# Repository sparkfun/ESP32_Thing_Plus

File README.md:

SparkFun ESP32 Thing Plus
========================================

[*SparkFun ESP32 Thing Plus (WRL-15663)*](https://www.sparkfun.com/products/15663)

The [SparkFun ESP32 Thing Plus](https://www.sparkfun.com/products/15663) is a comprehensive development platform for [Espressif's ESP32](https://espressif.com/en/products/hardware/esp32/overview). Like the 8266 and ESP32 Thing, the ESP32 Thing Plus is a **WiFi**-compatible microcontroller with support for **Bluetooth low-energy** (i.e BLE, BT4.0, Bluetooth Smart), a Qwiic adapter, and 21 I/O pins. Add to that a rich set of peripherals ranging from capacitive touch sensors, SD card interface, Ethernet, high-speed SPI, UART, I2S and I<sup>2</sup>C.

Upgraded and easy to use, the Esp32 Thing Plus will help make it the foundation of IoT and connected projects for many years to come.

Repository Contents
-------------------

* **/Hardware** - Eagle design files (.brd, .sch)
* **/Production** - Production panel files (.brd)

Documentation
--------------
* **[Hookup Guide](https://learn.sparkfun.com/tutorials/esp32-thing-plus-hookup-guide)** - Basic hookup guide for the ESP32 Thing Plus.
* **[SparkFun Fritzing repo](https://github.com/sparkfun/Fritzing_Parts)** - Fritzing diagrams for SparkFun products.
* **[SparkFun Graphical Datasheets](https://github.com/sparkfun/Graphical_Datasheets)** -Graphical Datasheets for various SparkFun products.

Product Versions
----------------
* [WRL-15663](https://www.sparkfun.com/products/15663)- v2.0, Slight hardware update that includes a 10&ohm; series resistor between VUSB and CP2102
* [WRL-14689](https://www.sparkfun.com/products/14689)- v1.0, Initial Release

License Information
-------------------

This product is _**open source**_! 

Please review the LICENSE.md file for license information. 

If you have any questions or concerns on licensing, please contact technical support on our [SparkFun forums](https://forum.sparkfun.com/viewforum.php?f=152).

Distributed as-is; no warranty is given.

- Your friends at SparkFun.

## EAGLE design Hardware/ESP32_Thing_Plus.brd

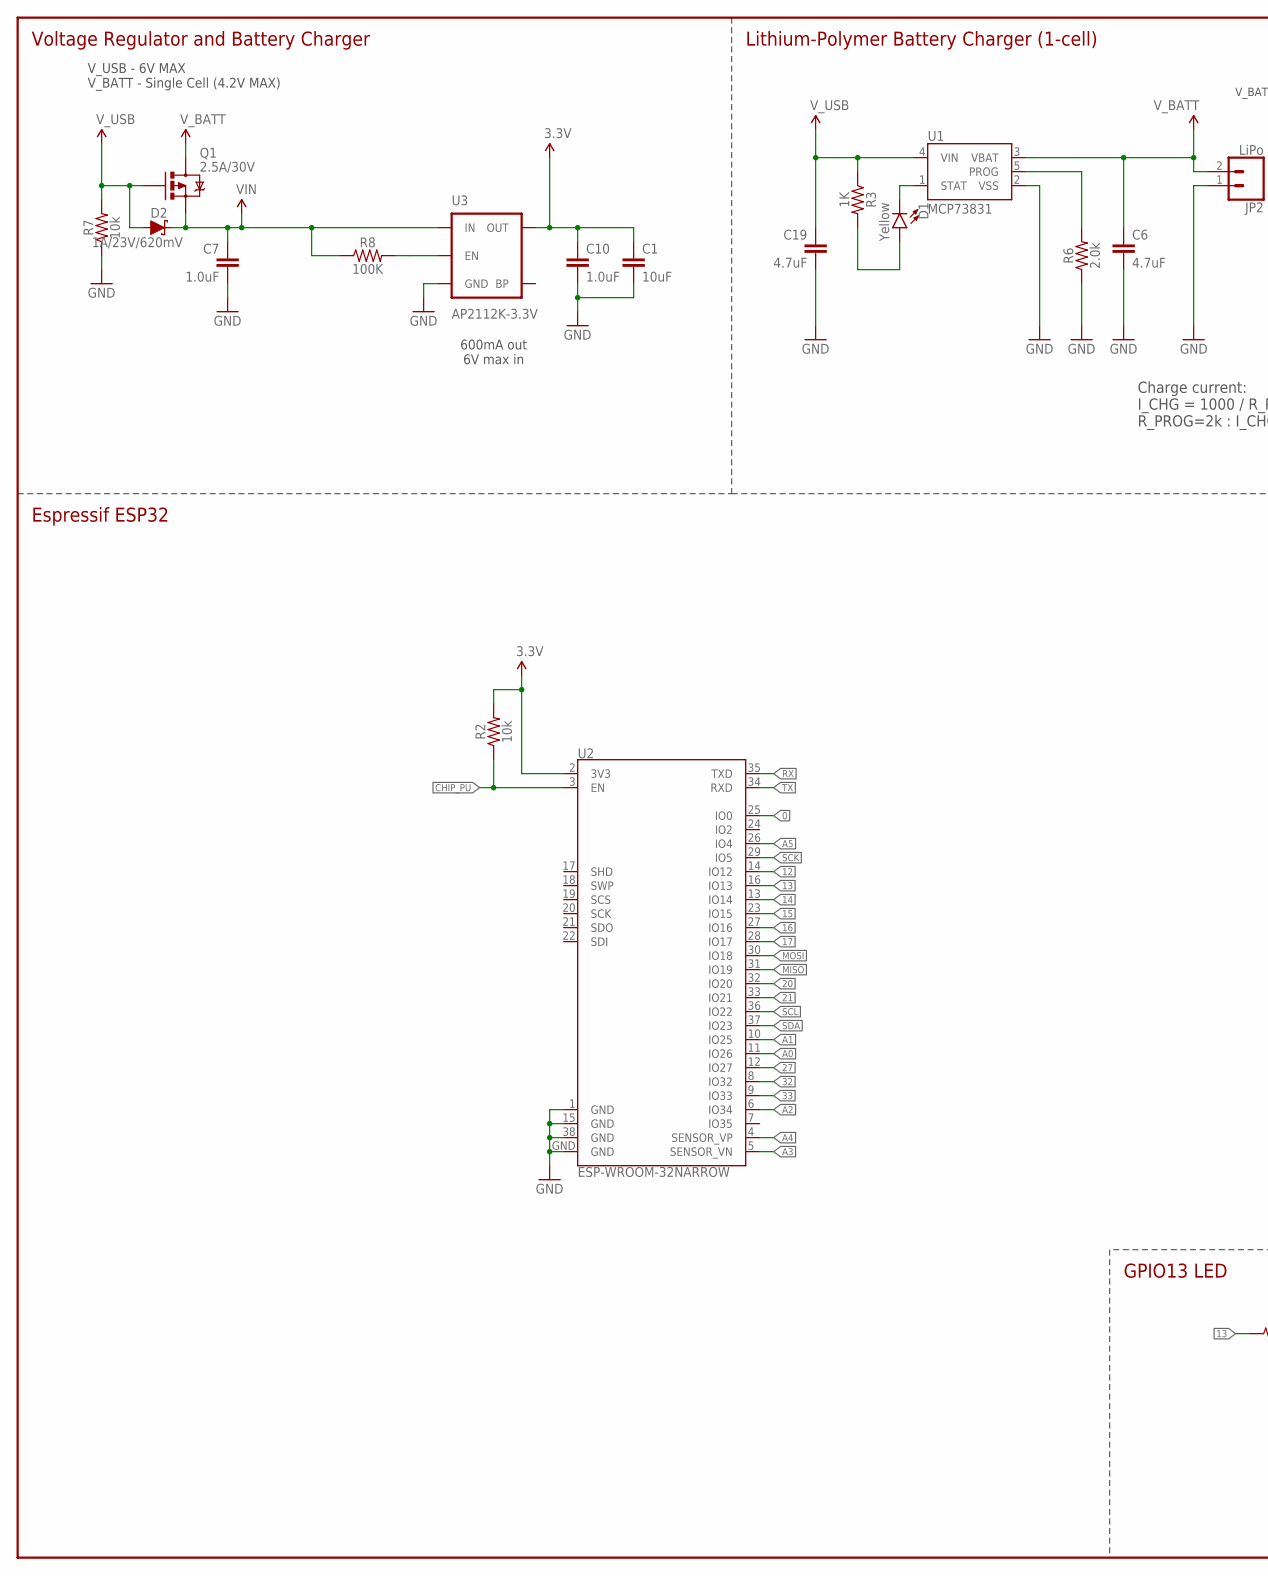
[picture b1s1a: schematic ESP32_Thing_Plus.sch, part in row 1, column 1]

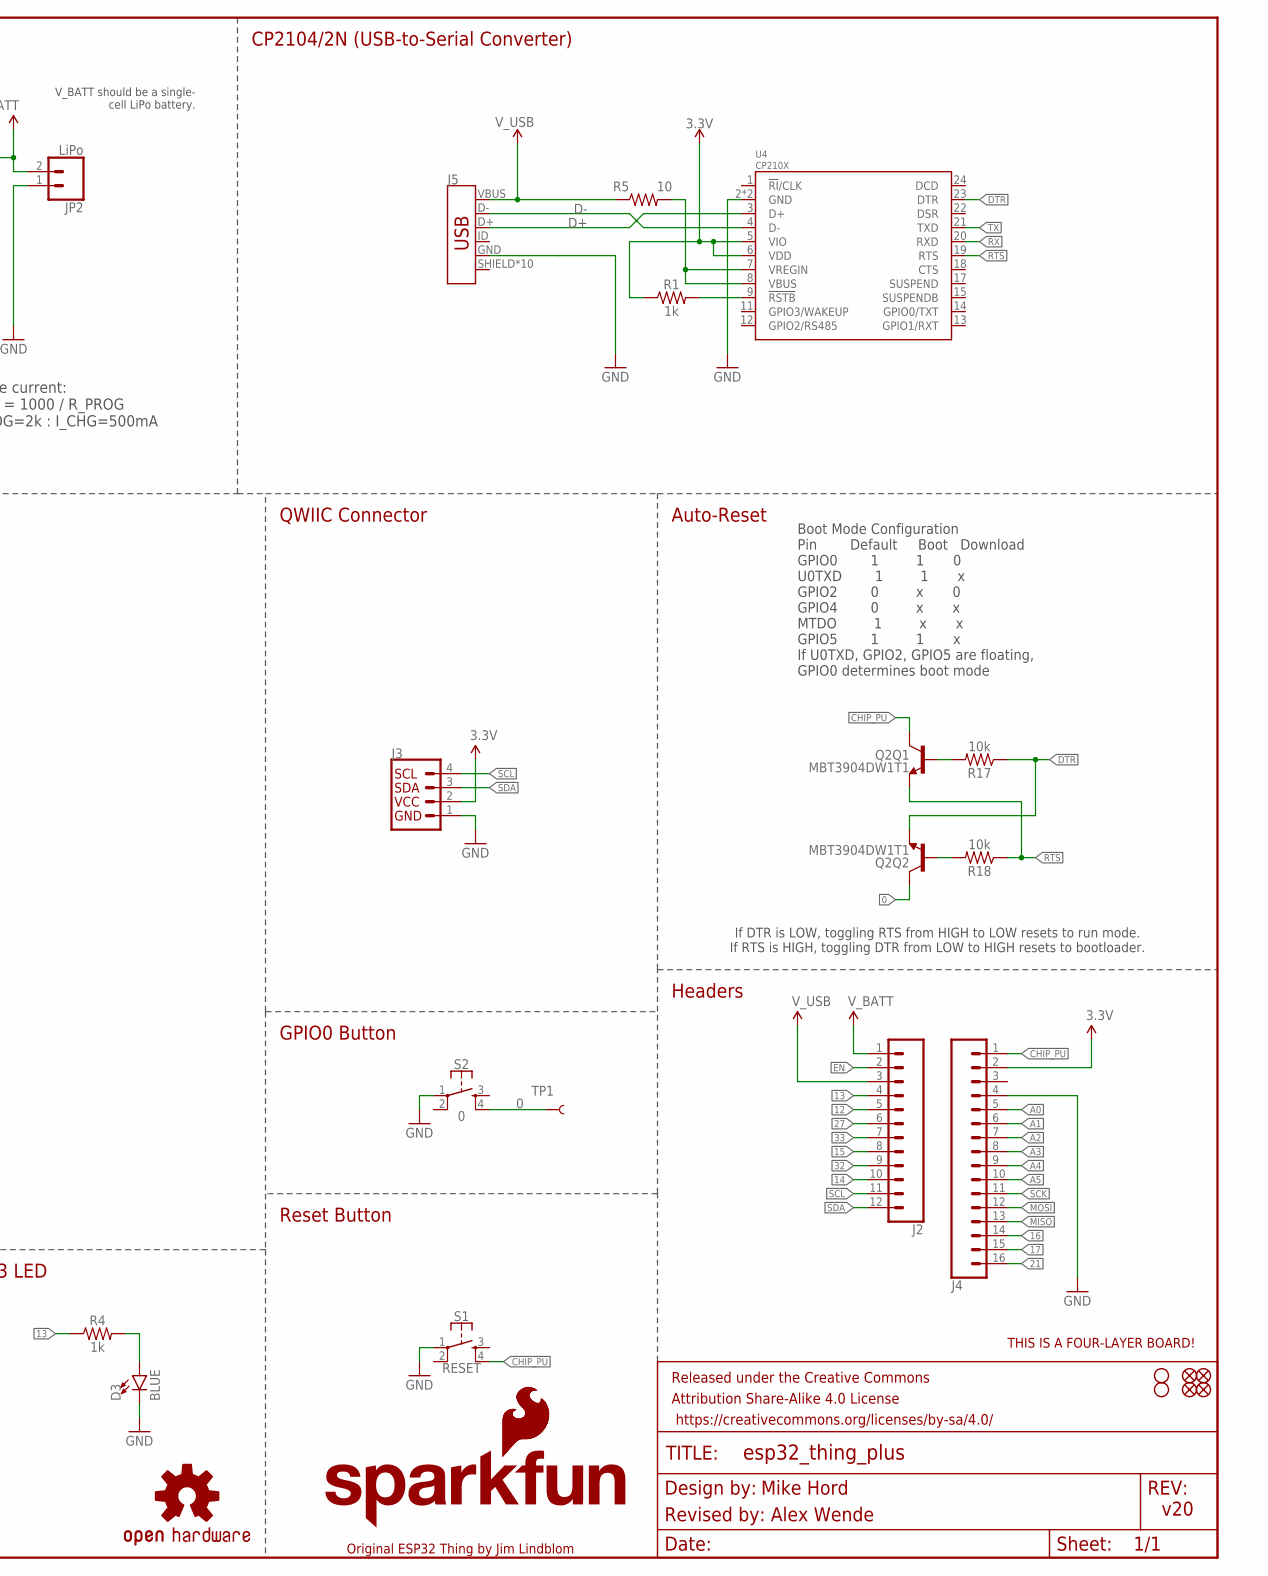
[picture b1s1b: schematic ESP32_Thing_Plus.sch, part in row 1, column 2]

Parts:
C1: 10uF; 0603
C6, C19: 4.7uF; 0603
C7: 1.0uF; 0603
C10: 1.0uF; 0402
D1: Yellow; LED-0603
D2: 1A/23V/620mV; SOD-323
D3: BLUE; LED-0603
FD1, FD2, FD3, FD4: FIDUCIALUFIDUCIAL; FIDUCIAL-MICRO
FRAME1: FRAME-LEDGER; CREATIVE_COMMONS
H1, H2: STAND-OFFTIGHT; STAND-OFF-TIGHT
J2: CONN_12SM_SQ_NO_SILK; 1X12_SM_SQ_NOSILK
J3: QWIIC_CONNECTORJS-1MM; 1X04_1MM_RA
J4: CONN_161X16_SM_SQ_NOSILK; 1X16_SM_SQ_NOSILK
J5: USB_MICRO-B_HALF_PTH_MILL; USB-MICROB-PTH-MILL
JP2: LiPo; JST-2-SMD
LOGO1: SFE_LOGO_FLAME.1_INCH; SFE_LOGO_FLAME_.1
LOGO2: OSHW-LOGOMINI; OSHW-LOGO-MINI
LOGO3: SFE_LOGO_NAME_FLAME.1_INCH; SFE_LOGO_NAME_FLAME_.1
LOGO4: FOUR_LAYER_WARNING
Q1: 2.5A/30V; SOT23-3@1
Q2: MBT3904DW1T1; SC70-6
R1, R4: 1k; 0603
R2, R7, R17, R18: 10k; 0603
R3: 1K; 0603
R5: 10; 0603
R6: 2.0k; 0603
R8: 100K; 0402
S1: RESET; TACTILE_SWITCH_SMD_4.6X2.8MM
S2: 0; TACTILE_SWITCH_SMD_4.6X2.8MM
TP1: TEST-POINTTP_15TH_THRU; TP_15TH
U1: MCP73831; SOT23-5
U2: ESP-WROOM-32NARROW; ESP-WROOM-32-NARROW
U3: AP2112K-3.3V; SOT23-5
U4: CP210X; QFN24

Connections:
0: Q2.6 (C), S2.4, TP1.P$1, U2.25 (IO0)
3.3V: C1.1, C10.1, J3.2, J4.2, R1.1, R2.2, U2.2 (3V3), U3.5 (OUT), U4.5 (VIO), U4.6 (VDD)
12: J2.5, U2.14 (IO12)
13: J2.4, R4.1, U2.16 (IO13)
14: J2.10, U2.13 (IO14)
15: J2.8, U2.23 (IO15)
16: J4.14, U2.27 (IO16)
17: J4.15, U2.28 (IO17)
20: U2.32 (IO20)
21: J4.16, U2.33 (IO21)
27: J2.6, U2.12 (IO27)
32: J2.9, U2.8 (IO32)
33: J2.7, U2.9 (IO33)
A0: J4.5, U2.11 (IO26)
A1: J4.6, U2.10 (IO25)
A2: J4.7, U2.6 (IO34)
A3: J4.8, U2.5 (SENSOR_VN)
A4: J4.9, U2.4 (SENSOR_VP)
A5: J4.10, U2.26 (IO4)
CHG: D1.C, U1.1 (STAT)
CHIP_PU: J4.1, Q2.3 (C), R2.1, S1.4, U2.3 (EN)
D+: J5.D+, U4.3 (D+)
D-: J5.D-, U4.4 (D-)
DTR: Q2.1 (E), R17.1, U4.23 (DTR)
EN: J2.2, R8.2, U3.3 (EN)
GND: C1.2, C6.2, C7.2, C10.2, C19.2, D3.C, J3.1, J4.4, J5.GND, JP2.1 (2), R6.1, R7.1, S1.1, S2.1, U1.2 (VSS), U2.1 (GND), U2.15 (GND), U2.38 (GND), U2.GND, U3.2 (GND), U4.2 (GND), U4.PAD (GND)
MISO: J4.13, U2.31 (IO19)
MOSI: J4.12, U2.30 (IO18)
unnamed: R1.2, U4.9 (!RSTB)
unnamed: D3.A, R4.2
unnamed: R5.2, U4.7 (VREGIN), U4.8 (VBUS)
unnamed: Q2.5 (B), R17.2
unnamed: Q2.2 (B), R18.2
unnamed: R6.2, U1.5 (PROG)
unnamed: D1.A, R3.2
RTS: Q2.4 (E), R18.1, U4.19 (RTS)
RX: U2.35 (TXD), U4.20 (RXD)
SCK: J4.11, U2.29 (IO5)
SCL: J2.11, J3.4, U2.36 (IO22)
SDA: J2.12, J3.3, U2.37 (IO23)
TX: U2.34 (RXD), U4.21 (TXD)
VIN: C7.1, D2.C, Q1.2 (S), R8.1, U3.1 (IN)
V_BATT: C6.1, J2.1, JP2.2 (1), Q1.3 (D), U1.3 (VBAT)
V_USB: C19.1, D2.A, J2.3, J5.VBUS, Q1.1 (G), R3.1, R5.1, R7.2, U1.4 (VIN)

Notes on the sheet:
Boot Mode Configuration Pin Default Boot Download GPIO0 1 1 0 U0TXD 1 1 x GPIO2 0 x 0 GPIO4 0 x x MTDO 1 x x GPIO5 1 1 x If U0TXD, GPIO2, GPIO5 are floating, GPIO0 determines boot mode
CP2104/2N (USB-to-Serial Converter)
V_BATT should be a single- cell LiPo battery.
Charge current: I_CHG = 1000 / R_PROG R_PROG=2k : I_CHG=500mA
Voltage Regulator and Battery Charger
Lithium-Polymer Battery Charger (1-cell)
600mA out 6V max in
Auto-Reset
Espressif ESP32
Reset Button
Headers
v20
Original ESP32 Thing by Jim Lindblom
If DTR is LOW, toggling RTS from HIGH to LOW resets to run mode. If RTS is HIGH, toggling DTR from LOW to HIGH resets to bootloader.
QWIIC Connector
Mike Hord
GPIO13 LED
GPIO0 Button
Revised by: Alex Wende
V_USB - 6V MAX V_BATT - Single Cell (4.2V MAX)

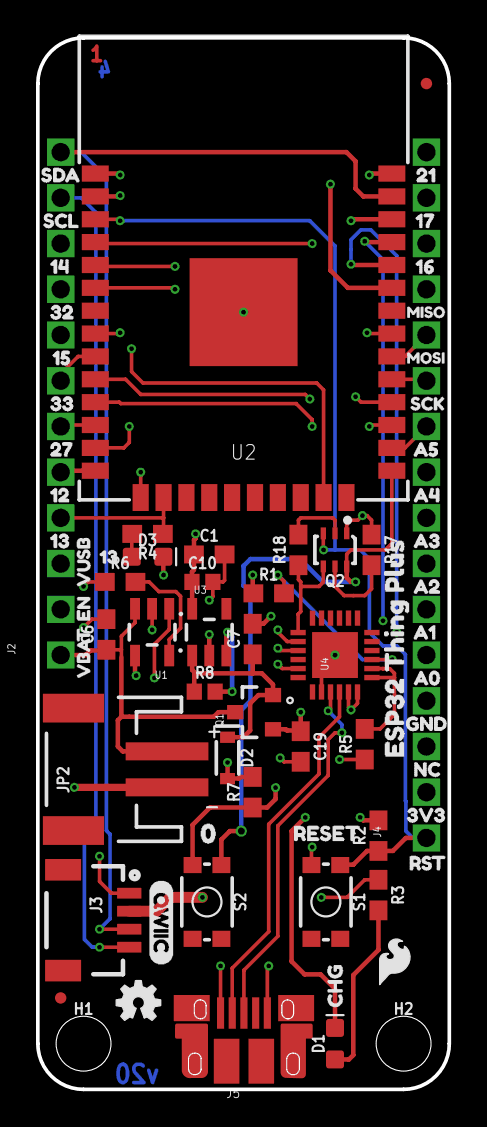
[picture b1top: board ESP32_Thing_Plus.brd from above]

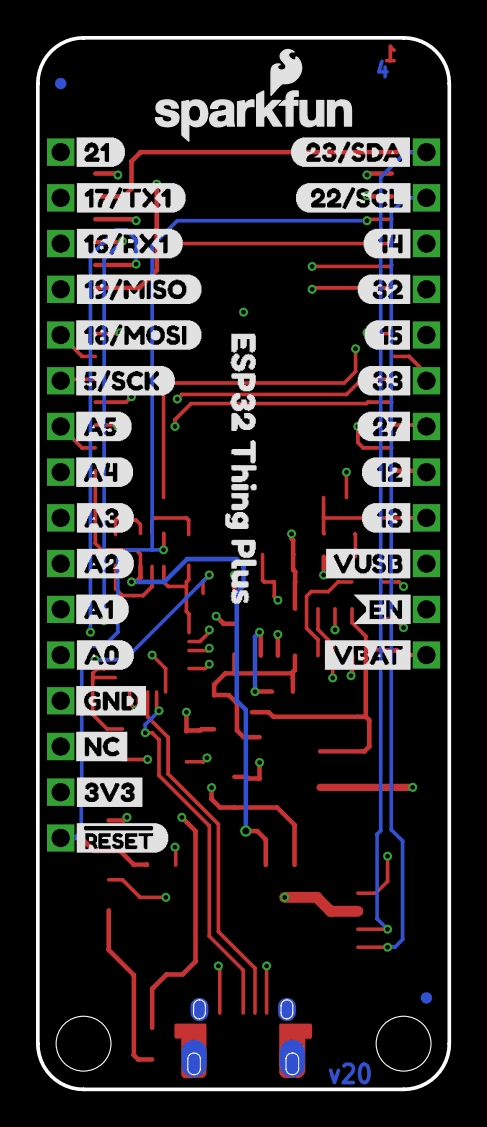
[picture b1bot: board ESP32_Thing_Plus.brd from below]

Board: 4 copper layers, 22.9 x 58.4 mm, 107 parts (32 on the bottom side), 43 nets.

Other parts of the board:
U$1: #RESET0
U$2: 3V31
U$3: 1323
U$4: 1417
U$5: 1519
U$6: 16#RX11
U$7: 17#TX10
U$8: 121
U$9: 210
U$10: 2721
U$11: 3218
U$12: 3320
U$13: A03
U$14: A14
U$15: A25
U$16: A36
U$17: A47
U$18: A58
U$19: EN26
U$20: GND2
U$21: 22#SCL1
U$22: 23#SDA0
U$23: QWIIC27
U$27: VBAT25
U$28: VUSB24
U$29: SDA1
U$30: SCL0
U$31: 142
U$32: 323
U$33: 154
U$34: 335
U$35: 276
U$36: 127
U$37: 138
U$38: 219
U$39: 1710
U$40: 1611
U$41: A515
U$42: A416
U$43: A317
U$44: A218
U$45: A119
U$46: A020
U$47: SCK20
U$48: GND21
U$49: NC22
U$50: VUSB8
U$51: EN9
U$52: VBAT10
U$53: 137
U$54: MISO0
U$55: MOSI1
U$56: CHG1
U$57: RESET0
U$58, U$65: ESP32_THING_PLUS0
U$59: ORDERING_INSTRUCTIONS
U$60: 3V323
U$61: RST24
U$62: 00
U$63: 5#SCK2
U$64: NC0
U$66: 18#MOSI1
U$67: 19#MISO0

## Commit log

2018-04-13 Initial changes to board design
2018-04-19 Ready for qc review
2018-04-19 Revised per QC double check
2018-04-25 Replaced EOL 1.0uF cap with newer one
2018-06-05 Feedback from review
2018-06-06 Fixes after QC review
2018-06-25 Changes from review, changed silk
2018-06-27 Add prod_id to wroom module
2018-08-14 v03 Changes
    -Updated size to 2.3x0.9in
    - Moved Qwiic connector to top
    - Adjusted inner layer copper pour
    - Cleaned up traces
2018-08-20 V03 Changes Cont.
    - Removed battery voltage divider
    - Increased Board name silk on bottom
    - Added NC buzzard labels to unconnected header pin.
    - Added button to GPIO-0
    - Swapped battery pins to match lipo battery pins
    - Fixed missing pin connections on USB transceiver.
2018-08-21 V03 QC Fixes
    - Replaced via on GPIO0 with test point via
2018-12-13 v10
    -Updated silk to include pin numbers and seondary functions for SPI/I2C/UART
    -Remapped a couple outer pins to match board definitions file
2018-12-13 v10 design review changes
    - Moved battery connector away from headers by 0.030"
    - Moved charge led and resistor away from standoff
    - Fixed silk on header pins 21 and 12
2018-12-13 v10 design review changes cont.
    Fixed pin 1 marker on dual NPN transistor
2018-12-17 v10 QC Fixes
    - Replaced drill hit with standoff
    - Added VCC range and battery type to schematic
    - Updated USB connector
2019-08-02 v20
    Added 10ohm series resistor between VUSB and CP2102
2019-08-20 Update ESP32_Thing_Plus.brd
    Updated Buzzard Labels
2020-01-09 Update README.md
    update links to latest version
2020-09-08 Updated USB to UART converter
    Updated shematic to indicate the USB to UART converter can be either the CP2104 or CP2102N
2021-03-19 Updated Attributes
    Changed U2 Prod_ID from IC-13849 to IC-15676

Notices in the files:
parts and their libraries:
SparkFun-Resistors: Licensing: Creative Commons ShareAlike 4.0 International - https://creativecommons.org/licenses/by-sa/4.0
SparkFun-Aesthetics: Released under the Creative Commons Attribution Share-Alike 4.0 License
SparkFun-Aesthetics: https://creativecommons.org/licenses/by-sa/4.0
